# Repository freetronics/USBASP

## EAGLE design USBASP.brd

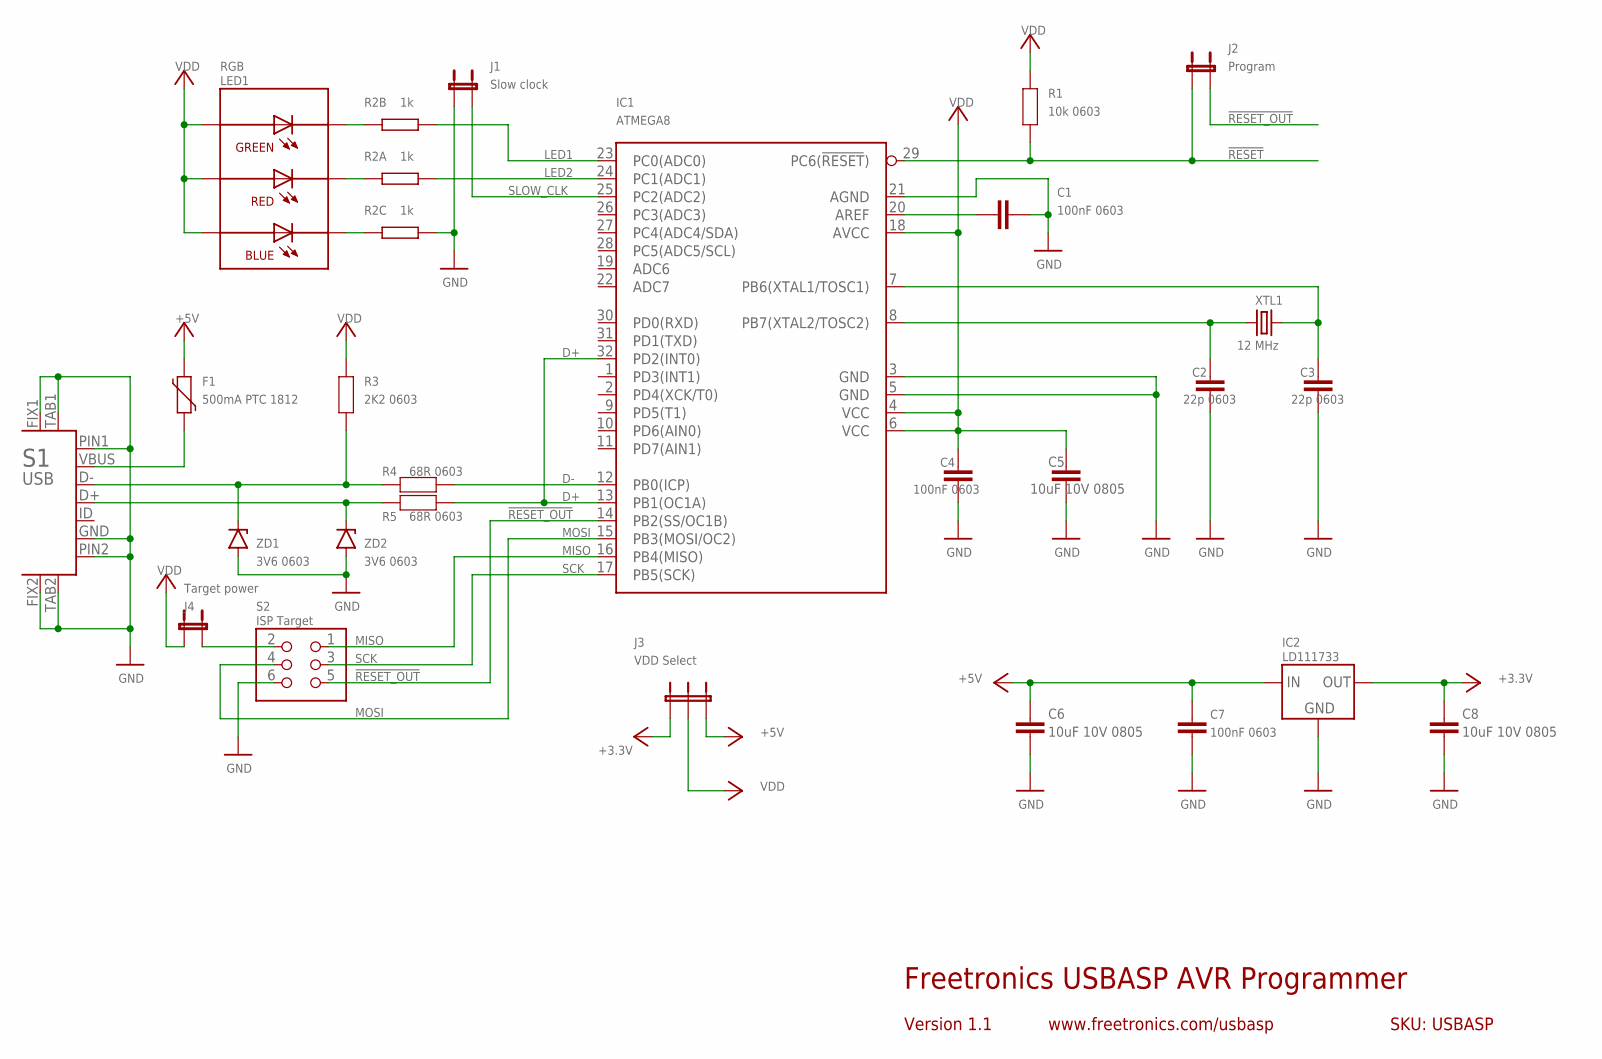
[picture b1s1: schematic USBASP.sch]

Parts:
C1, C4, C7: 100nF 0603; 0603
C2, C3: 22p 0603; 0603
C5, C6, C8: 10uF 10V 0805; C0805
F1: 500mA PTC 1812; 1812
IC1: ATMEGA8; TQFP32-08
IC2: LD111733; SOT-223
J1: Slow clock; HEADER_1X02
J2: Program; HEADER_1X02
J3: VDD Select; JUMPER_SPDT
J4: Target power; HEADER_1X02
LED1: RGB; 19-337
R1: 10k 0603; 0603
R2: 1k; CAY16
R3: 2K2 0603; 0603
R4, R5: 68R 0603; 0603
S1: USB; USB-MICROB-MB05PMXX
S2: ISP Target; HEADER_2X3
XTL1: 12 MHz; HC49US
ZD1, ZD2: 3V6 0603; MINIMELF

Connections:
!RESET: IC1.29 (PC6(!RESET!)), J2.1, R1.1
!RESET_OUT: IC1.14 (PB2(SS/OC1B)), J2.2, S2.5
+3V3: C8.1, IC2.2 (OUT), IC2.4 (OUT), J3.1
+5V: C6.1, C7.1, F1.2, IC2.3 (IN), J3.3
D+: IC1.13 (PB1(OC1A)), IC1.32 (PD2(INT0)), R5.1
D-: IC1.12 (PB0(ICP)), R4.1
GND: C1.2, C2.1, C3.1, C4.2, C5.2, C6.2, C7.2, C8.2, IC1.3 (GND), IC1.5 (GND), IC1.21 (AGND), IC2.1 (GND), J1.1, R2.3 (1), S1.FIX1, S1.FIX2, S1.GND, S1.PIN1, S1.PIN2, S1.TAB1, S1.TAB2, S2.6, ZD1.A, ZD2.A
LED1: IC1.23 (PC0(ADC0)), R2.2 (1)
LED2: IC1.24 (PC1(ADC1)), R2.1
MISO: IC1.16 (PB4(MISO)), S2.1
MOSI: IC1.15 (PB3(MOSI/OC2)), S2.4
unnamed: LED1.1 (C-B), R2.6 (2)
unnamed: LED1.2 (C-R), R2.8 (2)
unnamed: LED1.3 (C-G), R2.7 (2)
unnamed: J4.2, S2.2
unnamed: C3.2, IC1.7 (PB6(XTAL1/TOSC1)), XTL1.2
unnamed: C2.2, IC1.8 (PB7(XTAL2/TOSC2)), XTL1.1
unnamed: F1.1, S1.VBUS
unnamed: C1.1, IC1.20 (AREF)
unnamed: R5.2, S1.D+, ZD2.K
unnamed: R3.1, R4.2, S1.D-, ZD1.K
SCK: IC1.17 (PB5(SCK)), S2.3
SLOW_CLK: IC1.25 (PC2(ADC2)), J1.2
VDD: C4.1, C5.1, IC1.4 (VCC), IC1.6 (VCC), IC1.18 (AVCC), J3.2, J4.1, LED1.4 (A-B), LED1.5 (A-R), LED1.6 (A-G), R1.2, R3.2

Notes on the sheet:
Freetronics USBASP AVR Programmer
Version 1.1
www.freetronics.com/usbasp
SKU: USBASP

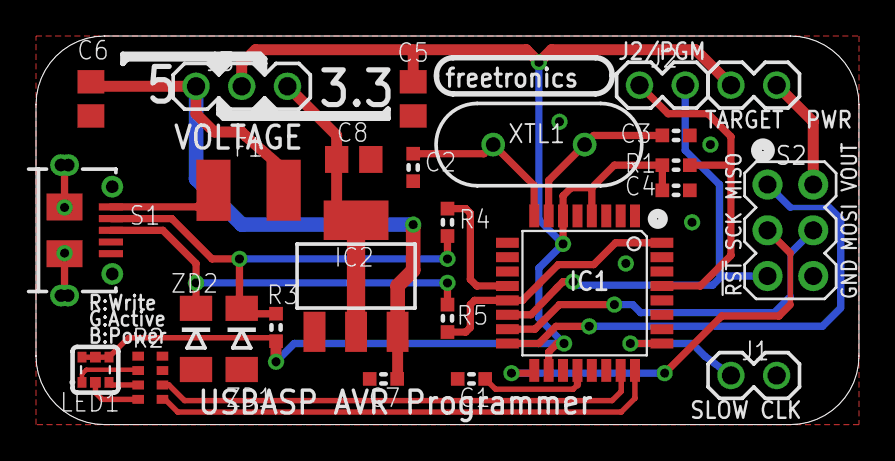
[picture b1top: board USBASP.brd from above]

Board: 2 copper layers, 45.7 x 21.6 mm, 26 parts (0 on the bottom side), 24 nets.

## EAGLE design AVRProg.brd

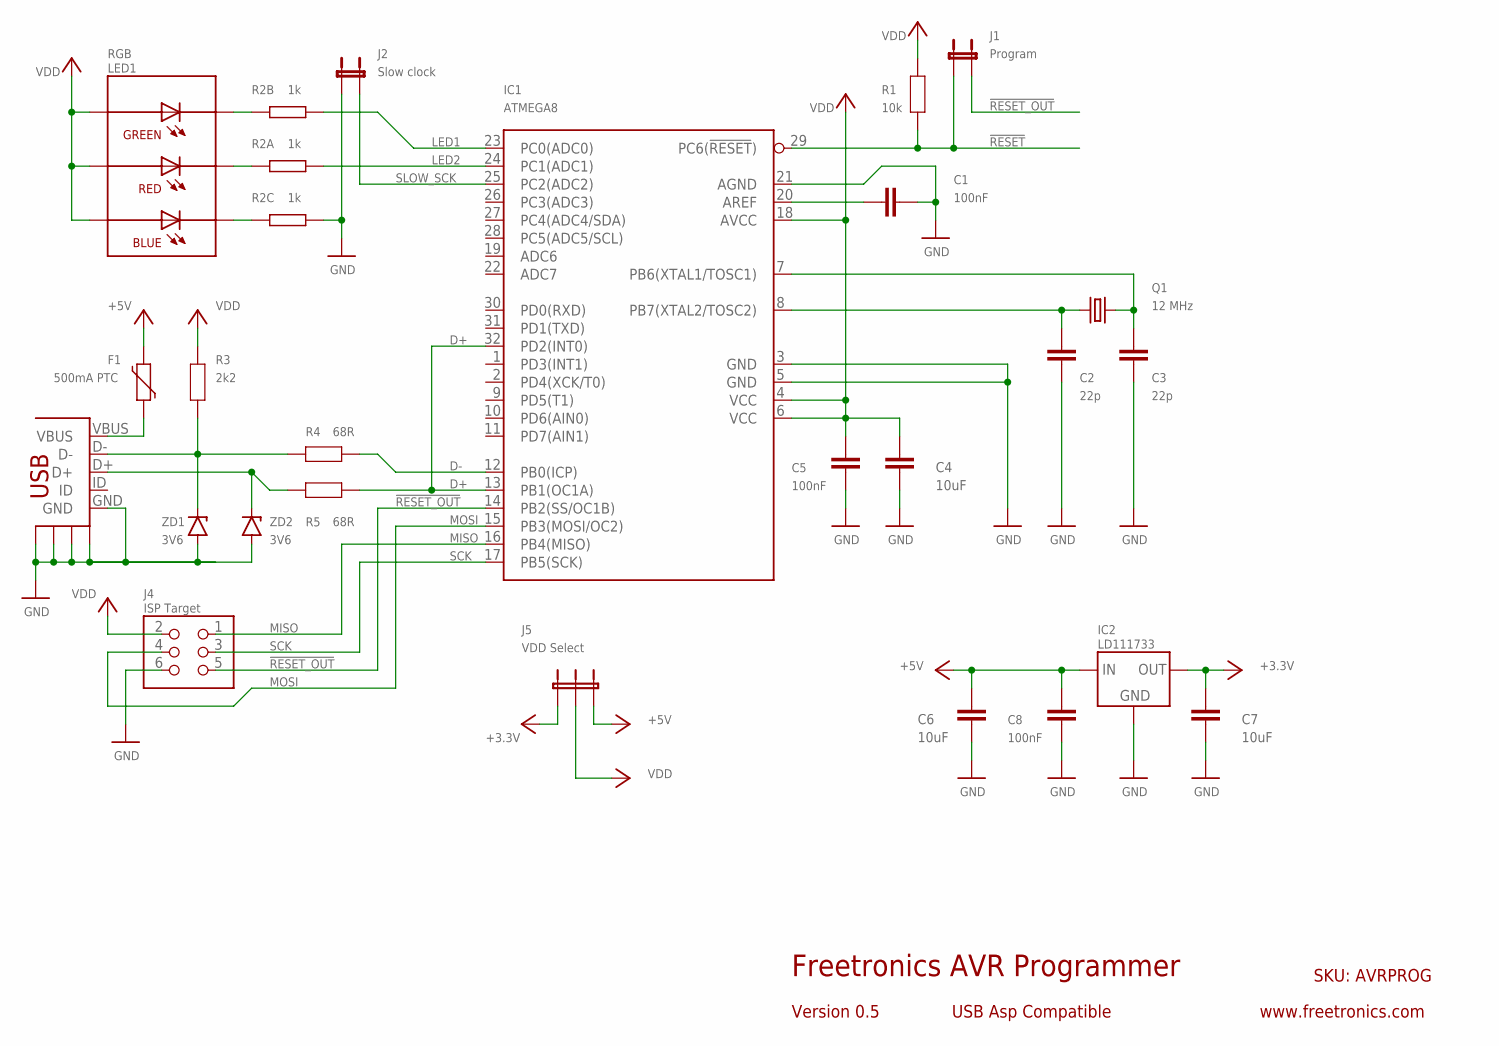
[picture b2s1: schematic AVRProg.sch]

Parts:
C1, C5, C8: 100nF; 0603
C2, C3: 22p; 0603
C4, C6, C7: 10uF; C0805
F1: 500mA PTC; 1812
IC1: ATMEGA8; TQFP32-08
IC2: LD111733; SOT-223
J1: Program; HEADER_1X02
J2: Slow clock; HEADER_1X02
J3: USB; USB-MINIB-FT
J4: ISP Target; HEADER_2X3
J5: VDD Select; JUMPER_SPDT
LED1: RGB; 19-337
Q1: 12 MHz; HC49US
R1: 10k; 0603
R2: 1k; CAY16
R3: 2k2; 0603
R4, R5: 68R; 0603
ZD1, ZD2: 3V6; MINIMELF

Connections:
!RESET: IC1.29 (PC6(!RESET!)), J1.1, R1.1
!RESET_OUT: IC1.14 (PB2(SS/OC1B)), J1.2, J4.5
+3V3: C7.1, IC2.2 (OUT), IC2.4 (OUT), J5.1
+5V: C6.1, C8.1, F1.2, IC2.3 (IN), J5.3
D+: IC1.13 (PB1(OC1A)), IC1.32 (PD2(INT0)), R5.1
D-: IC1.12 (PB0(ICP)), R4.1
GND: C1.2, C2.1, C3.1, C4.2, C5.2, C6.2, C7.2, C8.2, IC1.3 (GND), IC1.5 (GND), IC1.21 (AGND), IC2.1 (GND), J2.1, J3.GND, J3.SH1 (SH$1), J3.SH2 (SH$2), J3.SH3 (SH$3), J3.SH4 (SH$4), J4.6, R2.3 (1), ZD1.A, ZD2.A
LED1: IC1.23 (PC0(ADC0)), R2.2 (1)
LED2: IC1.24 (PC1(ADC1)), R2.1
MISO: IC1.16 (PB4(MISO)), J4.1
MOSI: IC1.15 (PB3(MOSI/OC2)), J4.4
unnamed: LED1.1 (C-B), R2.6 (2)
unnamed: LED1.2 (C-R), R2.8 (2)
unnamed: LED1.3 (C-G), R2.7 (2)
unnamed: C3.2, IC1.7 (PB6(XTAL1/TOSC1)), Q1.2
unnamed: C2.2, IC1.8 (PB7(XTAL2/TOSC2)), Q1.1
unnamed: F1.1, J3.VBUS
unnamed: C1.1, IC1.20 (AREF)
unnamed: J3.D+, R5.2, ZD2.K
unnamed: J3.D-, R3.1, R4.2, ZD1.K
SCK: IC1.17 (PB5(SCK)), J4.3
SLOW_SCK: IC1.25 (PC2(ADC2)), J2.2
VDD: C4.1, C5.1, IC1.4 (VCC), IC1.6 (VCC), IC1.18 (AVCC), J4.2, J5.2, LED1.4 (A-B), LED1.5 (A-R), LED1.6 (A-G), R1.2, R3.2

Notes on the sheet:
Freetronics AVR Programmer
Version 0.5
USB Asp Compatible
www.freetronics.com
SKU: AVRPROG

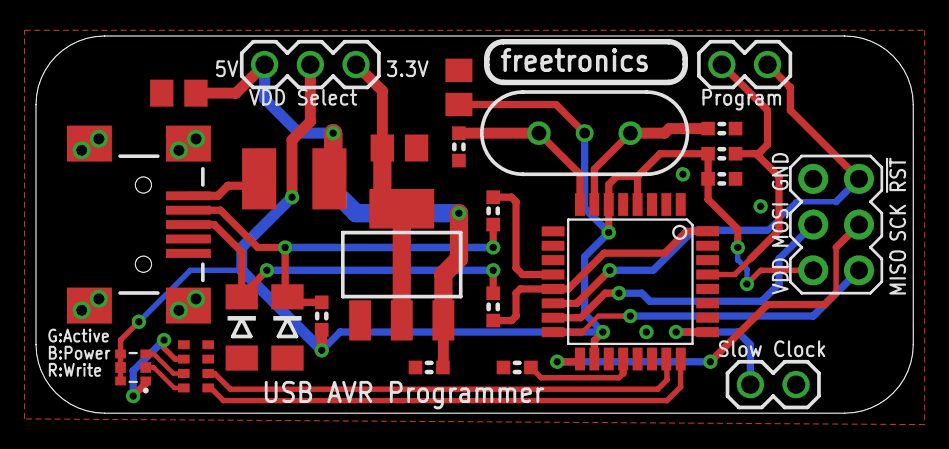
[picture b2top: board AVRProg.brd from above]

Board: 2 copper layers, 48.7 x 21.0 mm, 25 parts (0 on the bottom side), 23 nets.

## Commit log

2012-05-16 changed zeners to miniMELF, moved jumpers to increase clearance around ISP header, added 10uF cap on 5V rail.
2012-09-26 Schematic and layout improvements
2013-04-07 Renamed project to USBASP
2013-04-07 Renamed project
2013-04-07 Updates for v1.0 release
2013-04-16 Added jumper to enable / disable target power; improved labels

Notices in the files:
USBASP.brd:
(c) 2013 Freetronics Pty Ltd
Licensed under the TAPR
Open Hardware License
